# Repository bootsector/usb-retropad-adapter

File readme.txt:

USB RetroPad Adapter
(c)2011/2012 - Bruno Freitas - bootsector@ig.com.br
See COPYING.TXT for licensing information.

About
-----

USB RetroPad Adapter is a USB port of the Wii RetroPad Adapter. It allows you
to use the following classic controllers in your PC, Mac or PS3:

:. Sega Genesis pad(also supports: Sega Master System, Atari 2600 and others)

:. Nintendo NES pad

:. Super NES pad 

:. Playstation digital pads and Playstation 2 pads

:. Game Cube pad

:. Nintendo 64 pad

USB RetroPad Adapter also comes with handy screw terminal connectors, allowing
you to hook up a homemade arcade control to it and and use it to play your favo-
rite games on your PC or PS3!

How to get it
-------------

USB RetroPad Adapter is Opensource / Open hardware, so you can construct your
PCB, compile the source code, burn the firmware in the micro-controller and
start using it. 

However, there are people who are not familiar with PCB manufacturing process
nor have the skills, or even time, to construct his/her own adapter. For those
people, you are invited to contact me at bootsector@ig.com.br so I can sell
you a ready-to-use adapter! :)

You will also be able to buy it from both http://www.brunofreitas.com/ or
http://www.faiscaefumaca.com.br/

Legal
-----

USB RetroPad Adapter source code (software) is licensed under GPLv3.

USB RetroPad Adapter is open hardware licenced under Creative Commons 
Attribution-ShareAlike 3.0 Unported License. 

Acknowledgements
----------------

Thanks goes out to all people below. Without their work, this project wouldn't
be possible:

:. Roberto Oliveira for all the help with the PCB and "hardware" stuff.

:. Bill Porter for his PS2X Arduino library

:. The Arduino Team

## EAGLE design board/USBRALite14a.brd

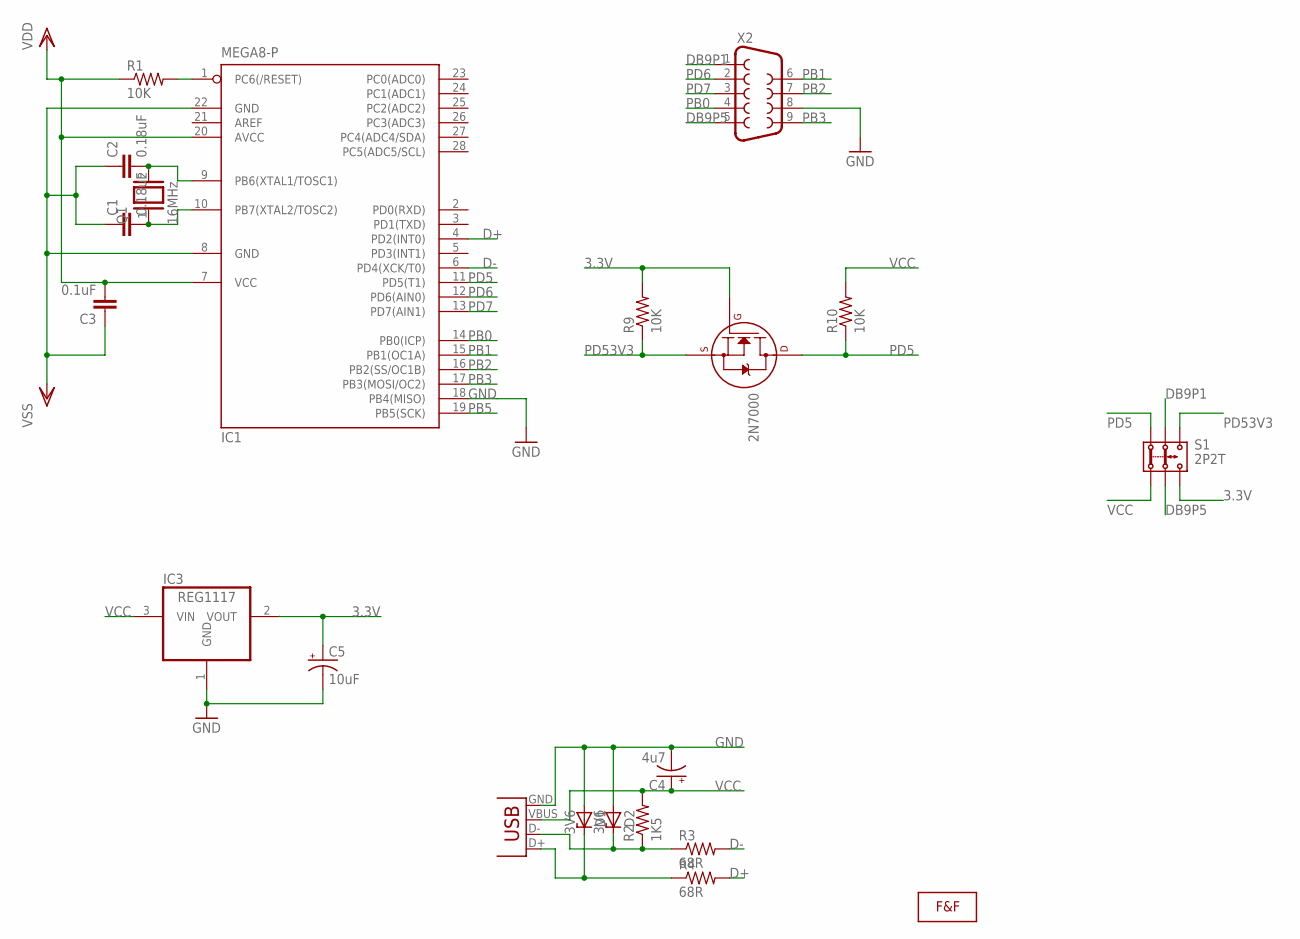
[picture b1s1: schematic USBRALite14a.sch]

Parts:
2N7000: 2N7000_TO92; TO-92
C1, C2: 0.18uF; C050-024X044
C3: 0.1uF; C050-024X044
C4: 4u7; E2,5-6
C5: 10uF; E2,5-6
D1, D2: 3V6; ZDIO-5
IC1: MEGA8-P; DIL28-3
IC3: REG1117; SOT223
Q1: 16MHz; QS
R1, R9, R10: 10K; 0207/10
R2: 1K5; 0207/10
R3, R4: 68R; 0207/10
S1: 2P2T
U$1: LOGOLOGO_WITHOUT_SMOKE_SMALL; LOGO2_SMALL
X1: USBPTH; USB-B-PTH
X2: DB9MALE; DB9_MALE

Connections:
3.3V: 2N7000.2 (G), C5.+, IC3.2 (VOUT), R9.2, S1.3.2
D+: IC1.4 (PD2(INT0)), R4.2
D-: IC1.6 (PD4(XCK/T0)), R3.2
DB9P1: S1.2.1, X2.1
DB9P5: S1.2.2, X2.5
GND: C1.1, C2.1, C3.1, C4.-, C5.-, D1.A, D2.A, IC1.8 (GND), IC1.18 (PB4(MISO)), IC1.22 (GND), IC3.1 (GND), X1.GND, X2.8
unnamed: IC1.1 (PC6(/RESET)), R1.2
unnamed: C2.2, IC1.9 (PB6(XTAL1/TOSC1)), Q1.2
unnamed: C1.2, IC1.10 (PB7(XTAL2/TOSC2)), Q1.1
unnamed: D1.C, R4.1, X1.D+
unnamed: D2.C, R2.1, R3.1, X1.D-
PB0: IC1.14 (PB0(ICP)), X2.4
PB1: IC1.15 (PB1(OC1A)), X2.6
PB2: IC1.16 (PB2(SS/OC1B)), X2.7
PB3: IC1.17 (PB3(MOSI/OC2)), X2.9
PB5: IC1.19 (PB5(SCK))
PD5: 2N7000.3 (D), IC1.11 (PD5(T1)), R10.1, S1.1.1
PD6: IC1.12 (PD6(AIN0)), X2.2
PD7: IC1.13 (PD7(AIN1)), X2.3
PD53V3: 2N7000.1 (S), R9.1, S1.3.1
VCC: C3.2, C4.+, IC1.7 (VCC), IC1.20 (AVCC), IC3.3 (VIN), R1.1, R2.2, R10.2, S1.1.2, X1.VBUS

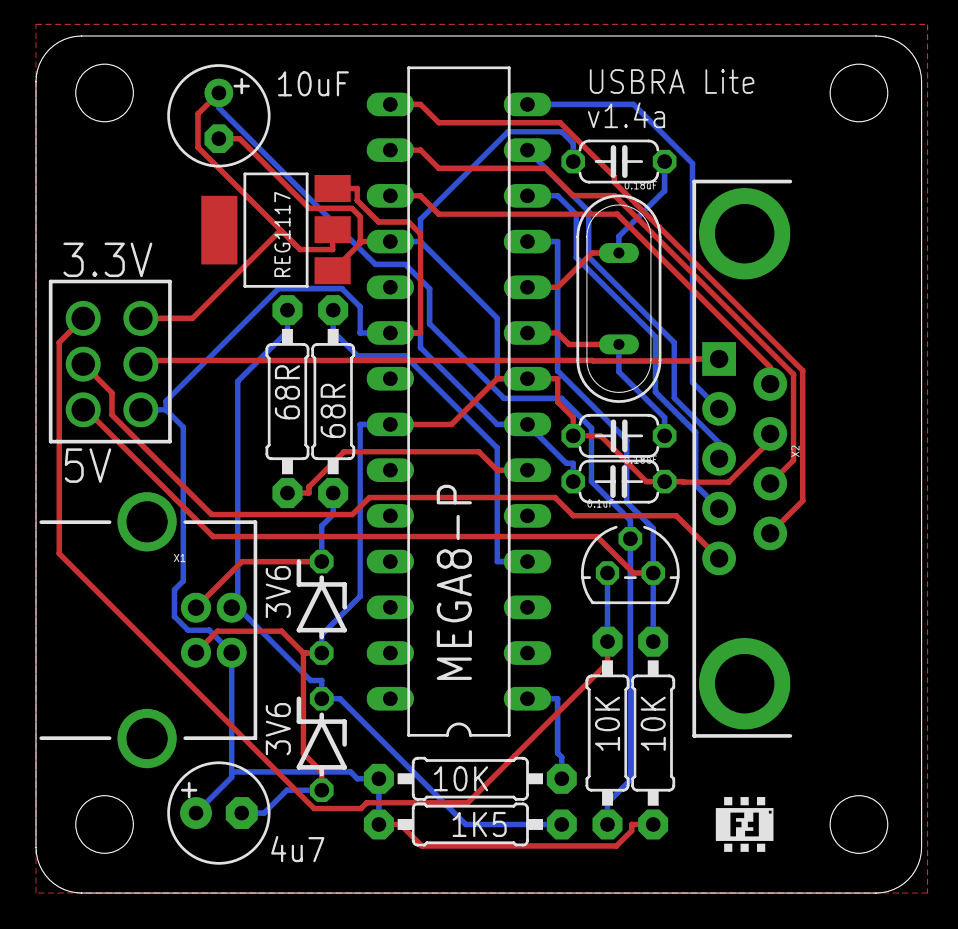
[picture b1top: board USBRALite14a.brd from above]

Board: 2 copper layers, 49.2 x 47.6 mm, 21 parts (0 on the bottom side), 20 nets.

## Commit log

2012-01-08 Uploaded board image.
2012-01-09 Updated board files to Rev.1.
2012-01-09 Code cleanup inside GC and N64 controller functions.
2012-01-09 Added 68R resistors value to schematics.
2012-01-09 Added Makefile support for atmega168p.
2012-01-10 Added svg file for acrylic laser cut.
2012-01-10 Stopped using watchdog because joystick was getting connected/disconnected in Linux.
2012-01-11 - DB9 pins 1 and 5 had voltage dropped to 3.3V in order to respect N64 and GC pads voltage. It shouldn't bring problems to other pads. To be tested...
    - 4021 arrangement data pin changed to a separate pin on atmega.
2012-01-11 Changed NESPad class so it allows defining clock, latch and data pins via constructor, so it works with a different data pin for the Arcade shiftin.
    Updated licensing info in some files.
2012-01-11 Oops!
2012-01-12 Corrected clock and latch pins for Arcade protocol.
2012-01-12 Fixed schematics and board files with proper MOSFET resistor (2N7000) for voltage shift between atmega (5V) and N64/GC contollers (3.4V).
    Corrected DB9/Arcade selection code.
2012-01-14 Added clearance for PCB standoffs. Repositioned LM137 as well for easier bending.
2012-01-14 Added top lasercut SVG.
2012-01-16 Added support for L3 and R3 buttons.
2012-01-16 Last remaining button from arcade_loop function set to L3.
2012-02-03 Disabled BOD in the uC fuses. Tries to initialize PS2/PSX pad only once.
2012-02-03 Reverted fuses config.
2012-02-04 Added USB RetroPad Adapter Lite 1.0 board/acrylic files.
2012-02-05 Disabled Timer 0 Overflow Interrupt inside vs_init() function. This interrupt is enabled by Arduino's init() function and it was making the PS3 to have dificulties trying to detect the adapter.
2012-02-06 Now that Timer0 overflow interrupt is disabled, it's important to NOT use Arduino's millis(), delay() and micros() functions, as they rely on that interrupt to work. PSX2 library seems to work fine a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
2012-02-06 Stopped using Bill Porter's PSX/PS2 lib because it relies on Arduino timer functions. Now using a much more simplified, yet VERY functional library, that don't make use of millis(), micros() or delay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
2012-02-07 Optimized PSX/PS2 pad library a little.
2012-02-07 Improved PSX pad library.
2012-02-07 Improved PSX/PS2 pad routines.
2012-02-08 Reverted back to Bill Porter's PSX/PS2 lib and changed it to not use delay() or millis().
2012-02-09 Small change in the PSX/PS2 pad polling routine.
2012-02-10 User manual draft.
2012-02-13 Minor user manual update.
2012-02-28 Updating analog axis values for square, circle, cross, triangle, l1, l2, r1, r2 buttons when necessary. Thanks Alan Chatham for the heads up!
2012-03-10 Corrected Arcade reading routine. Updated manual with correct Arcade pin/button mappings.
2012-03-10 Updated user manual.
2012-03-11 Commited board v1.2 files. No voltage regulator for N64/GC on-board anymore. There will be a new attachment board for regulating voltage for those joysticks.
2012-03-11 Updated 1.2 board eagle files. Added N64/GC voltage regulator board circuit.
2012-04-09 Commited new boards revision (1.3)
2012-04-25 Added Neo Geo controller support via external adapter (added eagle files for the adapter as well).
2012-04-27 GC and N64 driver now checks if a controller is not inserted and updates USB bus in case of controller timeout.
2012-05-01 ps2_loop() function now awaits for controller to be ready before entering main loop.
2012-05-05 Committed board revision 1.3a.
2012-05-10 Fixed arduino core so it compiles under newest avr-glibc versions (http://code.google.com/p/arduino/issues/detail?id=604).
2012-05-27 Added asm version of GC/N64 driver just in case future compiler versions mess with instructions (optimizations, etc...) in a way the time sensitive routines get off. Whenever that happens, use the as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
2012-05-28 Specified AVRDUDE_PROGRAMMER version in Makefiles (stk500v1) so programming works under Linux with latest avrdude revisions.
2012-05-28 Renamed GC/N64 driver asm code directory.
2012-06-09 :. Added one more pin to the pad detection routines (pin 4 - DB9) :. Added support for Sega Saturn pads (to be tested)
2012-06-09 DB9 pin 4 can't be used as a detection pin for Saturn pads because it may confuse PS2 pad detection (PS2 uses DB9 pin 4 as CLK signal).
    So, in order to get Sega Saturn pad support, you'll lose
    Sega Genesis/Master System/Atari, as Saturn pads uses almost as much
    pins from DB9 as Sega Genesis pads.
    So the default pad will be either Sega Genesis or Sega Saturn, and this
    is defined at compile time by setting the SATURN definition in the
    Makefile.
2012-06-09 Rewrite of the detectPad() routine so it takes care of PS2 pads/DB9 pin 4 usage. Now this should support Sega Saturn pads without losing support for Genesis pads.
2012-06-10 Fixed sega saturn controller extension diagram. Also fixed/improved some stuff in the sega saturn pad reading code.
2012-06-10 Changed digital pins handling functions from the "Fast" ones to the ordinary ones, as they were leading to wrong readings inside the pad detection routine.
2012-06-10 Merged XBOX branch files (still untested). Added Sega Saturn pad support to it.
2012-06-16 Working on XBOX!!! \o/
2012-06-16 XBOX driver code cleanup
2012-06-17 Added user manual for USB RetroPad Adapter for XBOX.
2012-06-26 Using a new PS2 pad driver (smaller one)
2012-06-27 Small bugfix
2012-06-30 Fixed NeoGeo pad support.
2012-06-30 NeoGeo pad support was broken for XBOX. Fixed.
2012-07-01 Implemented a BootloadHID bootloader so firmware can be self-updated in the future.
2012-07-01 DFU condition has changed from checking DB9 pin 1 to both DB9 pins 4 and 9 (grounded).
2012-07-01 bootloader now using properly all the pins involved in the pad detection algorithm.
2012-07-26 :. Improved PS2 driver :. Improved XBOX Pad driver
2012-07-27 PS2 pad driver tweak. Enabled watchdog for PC/Mac/PS3 USB.
2012-07-28 PS2 Pad driver: reverted to more aggressive interrupt disable. This makes the PS2 controller more responsive on XBOX (USB RetroPad Adapter). This can be disable so it still works on Wii RetroPad Adap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
2012-09-04 PS2 pad driver now detects analog mode during init.
2012-09-05 Treating Wii Classic Controller extension cable.
2012-09-08 XBOX version now is taking care of Wii Classic Controller extension properly.
2012-09-29 Fixed HOME button triggering condition (Master System pad Button 2 reports like C + START buttons).
2012-09-30 Fixed Sega Genesis controller driver so it works fine with Sega Master System, Atari 2600 and compatibles.
2013-01-03 Improved GCPad driver timing by making core read/write functions inline and adjusted the delay for the reading function.
2013-01-03 Added a 6ms delay between GC pad reads so don't get the controller too much stressed. Official games poll the controller using that interval.
2013-01-03 Tweaked delay time for GC pad readings
2013-04-20 Added support for the TurboGrafx 16 controller
2013-04-20 Added support for the TurboGrafx 16 controller (XBOX mode)
2013-04-21 Added TG16 extension cable schematics
2013-04-21 Fixed extension detection routine
2014-08-24 No .DS_Store files
2014-08-27 Changed email address in copyright disclaimers
2014-09-03 Added one more axis - Slider - for registering GC pads analog shoulders
2016-01-18 Fixed Arduino map() function. Fixed analog ranges for GC and N64 pads
2016-01-24 Fixed analog range for GC pad on XBOX
2016-01-25 Ignoring eclipse project files
2016-01-25 gitignore enforced
2016-01-25 Makes it compile on newer toolchains
2017-10-28 Added USB RetroPad Adapter v1.4 Lite PCB and gerber files - Using SMD based 3.3v voltage regulator
2017-11-03 Updated PCB to v1.4a with thicker traces
2017-11-25 Fixed Saturn Hori Arcade Stick compatibility
2017-11-27 atmega168 fuses config fix
